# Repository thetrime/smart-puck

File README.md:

# Smart Puck
> But what if we went _smaller_?

# Configuration
You need three config files to run smart-puck. See the README.md file in the `config` directory

# Prerequisites
Obviously you need the hardware. 
FIXME: Details to be filled in once I work out what the hardware is ^^

You also need:
   * python
   * pip

# Installation
A shell script is available for bash users. (`mpremote cp *.py :` doesn't work on Windows). A workaround is to stop using Windows.

You can install it by just running `./install.sh` after plugging in your pico. Note that you also have to flash the Micropython firmware to it first.

That's it. Reboot and it's ready!

# To do list
## Code
   * Nothing? That doesn't sound right
## Hardware
   * Finish the schematic and PCB design
   * Create a STL for the case

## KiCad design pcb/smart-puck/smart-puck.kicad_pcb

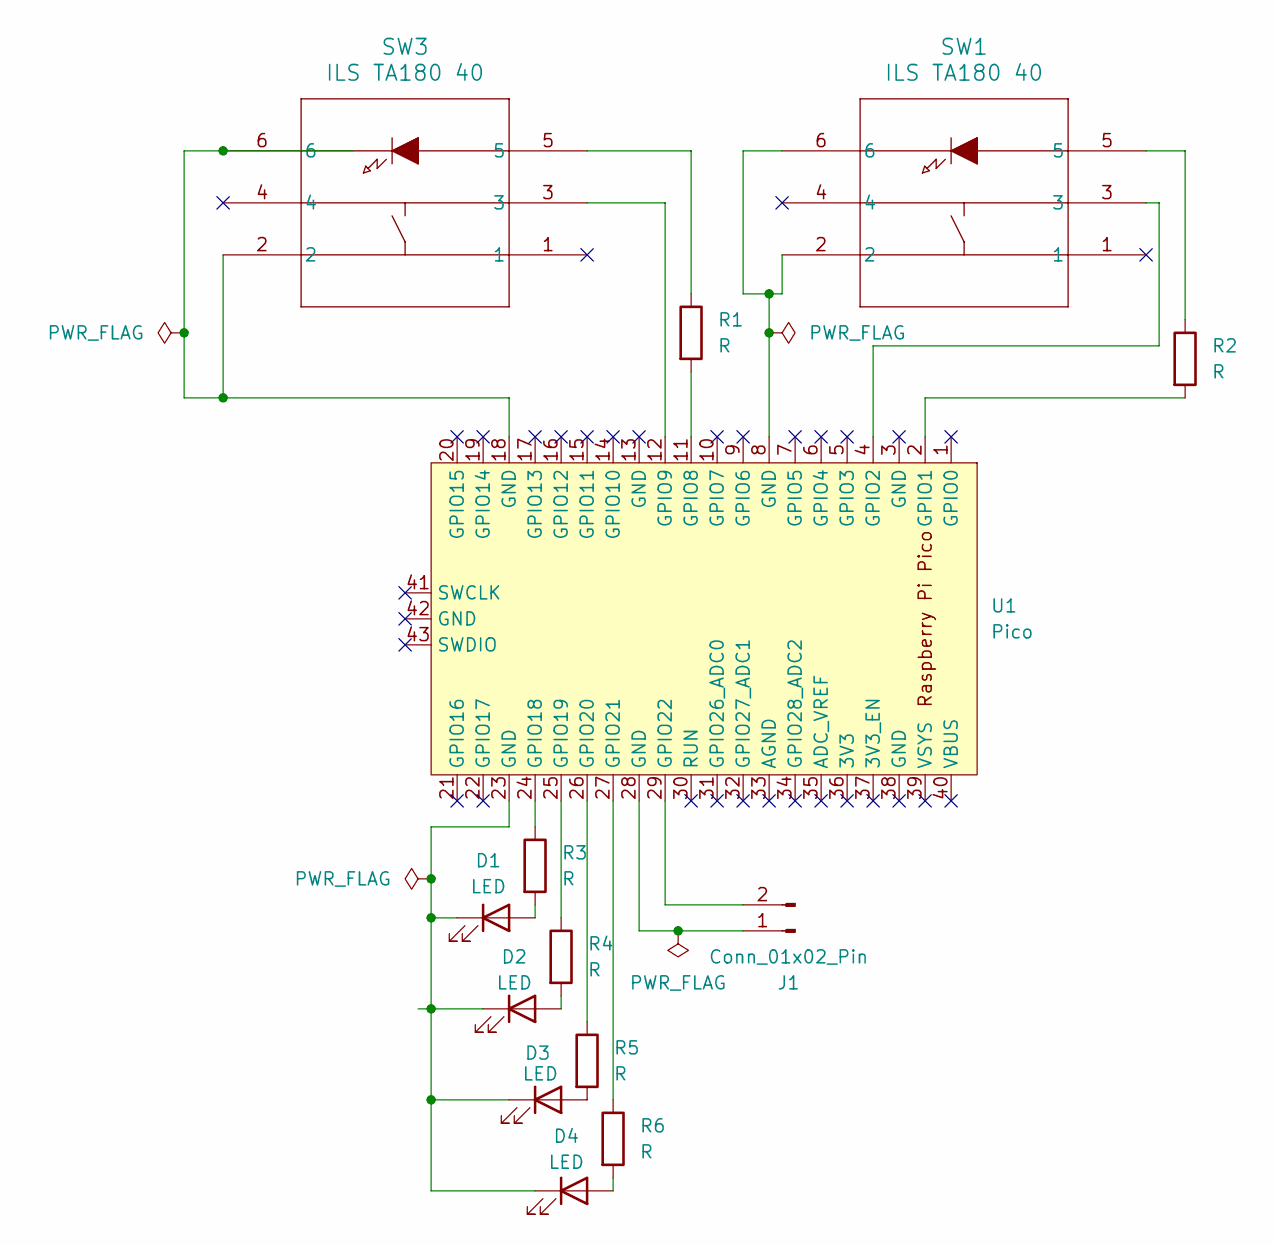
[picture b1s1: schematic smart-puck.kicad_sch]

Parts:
D1, D2, D3, D4: LED; LED_D5.0mm_Clear
J1: Conn_01x02_Pin; PinHeader_1x02_P2.54mm_Vertical
R1, R2, R3, R4, R5, R6: R; R_Axial_DIN0309_L9.0mm_D3.2mm_P12.70mm_Horizontal
SW1, SW3: ILS TA180 40; SW6_ILS TA180 40_CNK
U1: Pico; RPi_Pico_SMD_TH

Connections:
unnamed: D1.2 (A), R3.2
unnamed: D1.1 (K), D2.1 (K), D3.1 (K), D4.1 (K), U1.23 (GND)
unnamed: D2.2 (A), R4.2
unnamed: D3.2 (A), R5.2
unnamed: D4.2 (A), R6.2
unnamed: J1.1, U1.28 (GND)
unnamed: J1.2, U1.29 (GPIO22)
unnamed: R1.1, SW3.5
unnamed: R2.1, SW1.5
unnamed: SW1.2, SW1.6, U1.8 (GND)
unnamed: SW3.2, SW3.6, U1.18 (GND)
unnamed: R2.2, U1.2 (GPIO1)
unnamed: SW1.3, U1.4 (GPIO2)
unnamed: R1.2, U1.11 (GPIO8)
unnamed: SW3.3, U1.12 (GPIO9)
unnamed: R3.1, U1.24 (GPIO18)
unnamed: R4.1, U1.25 (GPIO19)
unnamed: R5.1, U1.26 (GPIO20)
unnamed: R6.1, U1.27 (GPIO21)

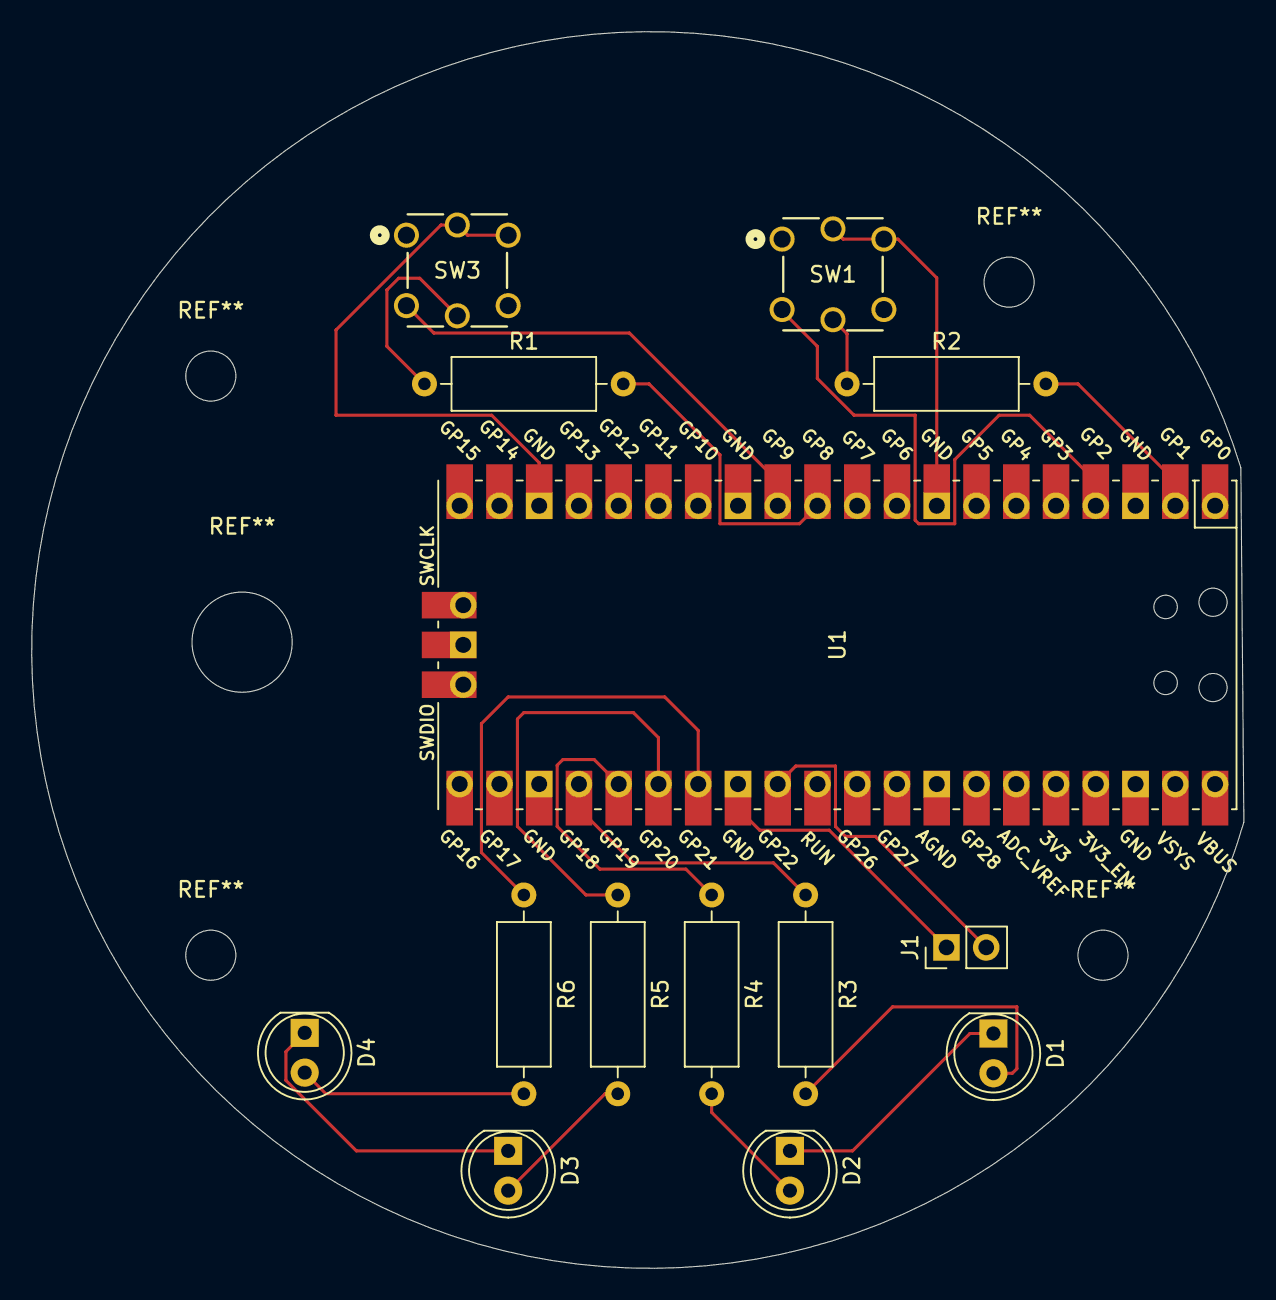
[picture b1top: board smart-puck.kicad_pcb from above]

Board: 2 copper layers, 77.4 x 79.0 mm, 14 parts (0 on the bottom side), 19 nets.

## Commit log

2025-02-02 Initial framework
2025-02-02 Initial airtag code works
2025-02-05 Restructure project significantly. Replace all the stuff micropython doesnt have with hand-written alternatives. Now I know how to do ECC arithmetic, I guess
2025-02-05 Address tiny loophole in curve calculations. I think this is right - thinking about the cartesian projection it checks out
2025-02-05 Tidy up code. Stop obscuring the system bluetooth with my own one
2025-02-05 Add Fife bin check code
2025-02-06 Ok, this is the skeleton. Now I just need to make it work
2025-02-07 Do not tell everyone my wifi details
2025-02-07 Update documentation
2025-02-08 Actually wait
2025-02-08 Oops
2025-02-08 Add install script
2025-02-08 Fix a multitude of bugs
2025-02-08 Do keyroll. Also the time needs to be set. The board has no way of knowing what the time is
2025-02-08 Some more tidying up. Maybe we dont have to run at full duty. Note that the key hydration takes FOREVER
2025-02-08 Log distance
2025-02-09 This is a bit faster, but only a bit
2025-02-09 Reimplement the NIST224p algorithms using Jacobian coordinates to see if it improves the performance
2025-02-09 Get rid of the affine version. Add a status LED. Roll the keys before we start scanning
2025-02-09 Do not run the performance test on load
2025-02-09 Add installer script
2025-02-09 Fix a typo. Also log where in the index we are to give an indicating of timing accuracy
2025-02-09 Start a todo list
2025-02-09 Restructure the repo so that all the source code is in a subdirectory
2025-02-09 Add the kicad project to git
2025-02-09 Update the install details
2025-02-09 Use exising LEDs for status
2025-02-09 Fix a few shortcomings with the airtag code
2025-02-11 Fix a multitude of bugs now I can test it on the device
2025-02-13 Fix missing second arg in callback
2025-02-13 Actually wire up the right pins. This all seems correct now
2025-02-13 Add doorbell socket. oops
2025-02-14 Tuning of distance
2025-02-14 Try and synchronise blinking if it makes sense
2025-02-14 More tweaks to various bits. That async callback was a big mistake
2025-02-14 update PCB. Align components. Add some mounting holes. Add a big hole in case we need to mount the doorbell stuff underneath
